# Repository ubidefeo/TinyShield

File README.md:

# TinyShield
A shield for programming ATTiny's from your Arduino

It's setup to just need 1 0805 Cap to put the Arduino into programming mode and a few headers to connect your Tiny's and to allow you to connect things easily to your tiny's once you've programmed them.

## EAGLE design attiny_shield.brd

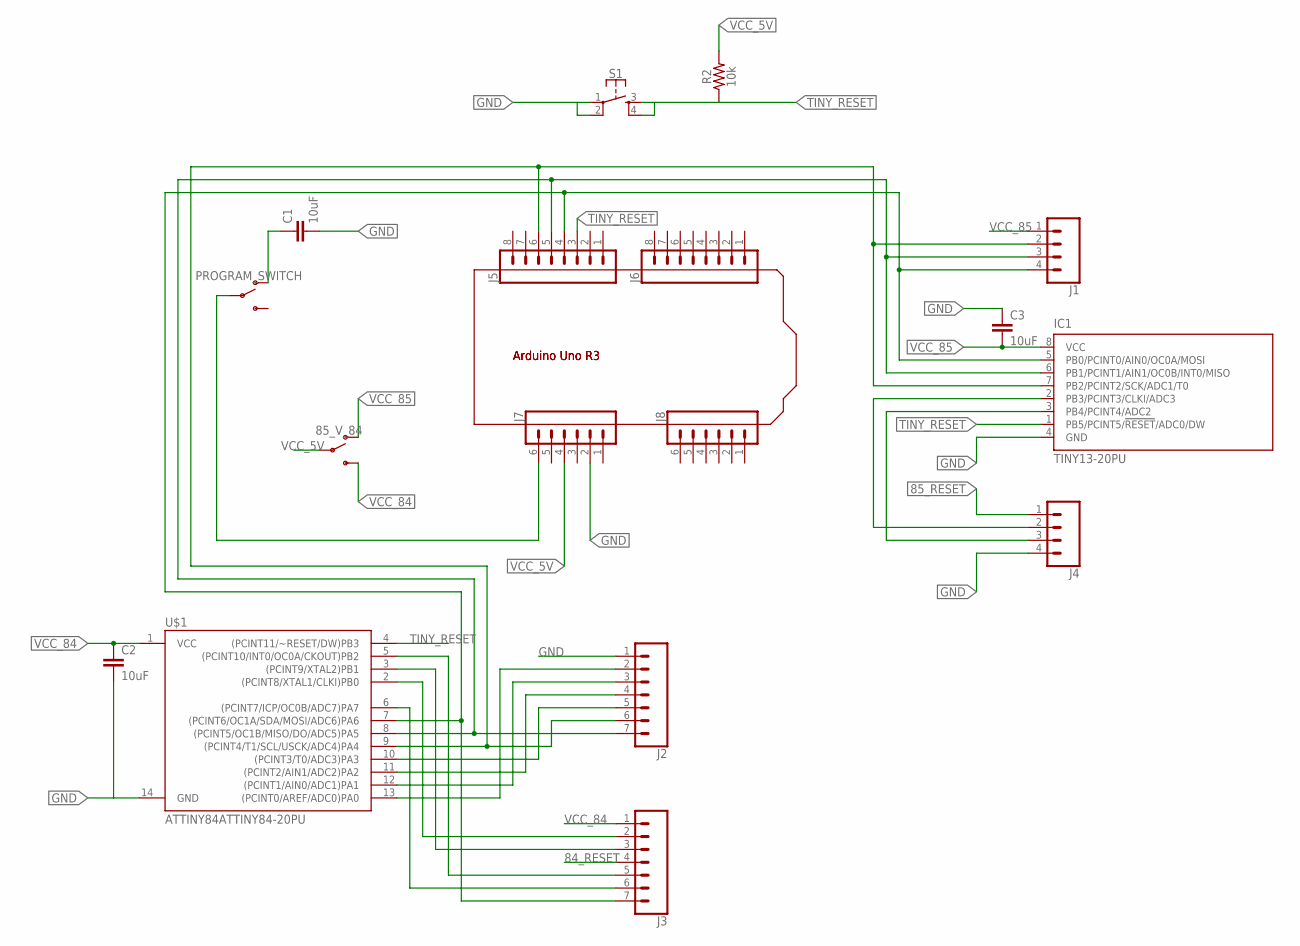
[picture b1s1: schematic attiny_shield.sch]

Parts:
85_V_84: SPARKFUN-SWITCHES_SWITCH-SPDT-SMD-AYZ0202; SPARKFUN-SWITCHES_SWITCH_DPDT_SMD_AYZ0202
C1, C2, C3: 10uF; 0805
IC1: TINY13-20PU; DIL08
J1, J4: CONN_04; 1X04
J2, J3: CONN_07; 1X07
J5, J6: CONN_08"; 1X08
J7, J8: CONN_06SILK_FEMALE_PTH; 1X06
PROGRAM_SWITCH: SWITCH-SPDT-SMD-AYZ0202; SWITCH_DPDT_SMD_AYZ0202
R2: 10k; SPARKFUN-RESISTORS_0603
S1: SPARKFUN-SWITCHES_MOMENTARY-SWITCH-SPST-2-SMD-5.2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; SPARKFUN-SWITCHES_TACTILE_SWITCH_SMD_5.2MM
U$1: ATTINY84ATTINY84-20PU; DIP14

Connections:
84_0: J2.2, U$1.13 ((PCINT0/AREF/ADC0)PA0)
84_1: J2.3, U$1.12 ((PCINT1/AIN0/ADC1)PA1)
84_RESET: J3.4
85_RESET: J4.1
GND: C1.2, C2.2, C3.1, IC1.4 (GND), J2.1, J4.4, J7.2, S1.1, S1.2, U$1.14 (GND)
MISO: IC1.6 (PB1/PCINT1/AIN1/OC0B/INT0/MISO), J1.3, J2.7, J5.5, U$1.8 ((PCINT5/OC1B/MISO/DO/ADC5)PA5)
MOSI: IC1.5 (PB0/PCINT0/AIN0/OC0A/MOSI), J1.4, J3.7, J5.4, U$1.7 ((PCINT6/OC1A/SDA/MOSI/ADC6)PA6)
unnamed: C1.1, PROGRAM_SWITCH.1 (O)
unnamed: IC1.2 (PB3/PCINT3/CLKI/ADC3), J4.2
unnamed: IC1.3 (PB4/PCINT4/ADC2), J4.3
unnamed: J7.6, PROGRAM_SWITCH.2
unnamed: J2.4, U$1.11 ((PCINT2/AIN1/ADC2)PA2)
unnamed: J2.5, U$1.10 ((PCINT3/T0/ADC3)PA3)
unnamed: J3.6, U$1.6 ((PCINT7/ICP/OC0B/ADC7)PA7)
unnamed: J3.2, U$1.2 ((PCINT8/XTAL1/CLKI)PB0)
unnamed: J3.3, U$1.3 ((PCINT9/XTAL2)PB1)
unnamed: J3.5, U$1.5 ((PCINT10/INT0/OC0A/CKOUT)PB2)
SCK: IC1.7 (PB2/PCINT2/SCK/ADC1/T0), J1.2, J2.6, J5.6, U$1.9 ((PCINT4/T1/SCL/USCK/ADC4)PA4)
TINY_RESET: IC1.1 (PB5/PCINT5/!RESET!/ADC0/DW), J5.3, R2.1, S1.3, S1.4, U$1.4 ((PCINT11/~RESET/DW)PB3)
VCC_5V: 85_V_84.2, J7.4, R2.2
VCC_84: 85_V_84.3 (S), C2.1, J3.1, U$1.1 (VCC)
VCC_85: 85_V_84.1 (O), C3.2, IC1.8 (VCC), J1.1

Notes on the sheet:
Arduino Uno R3

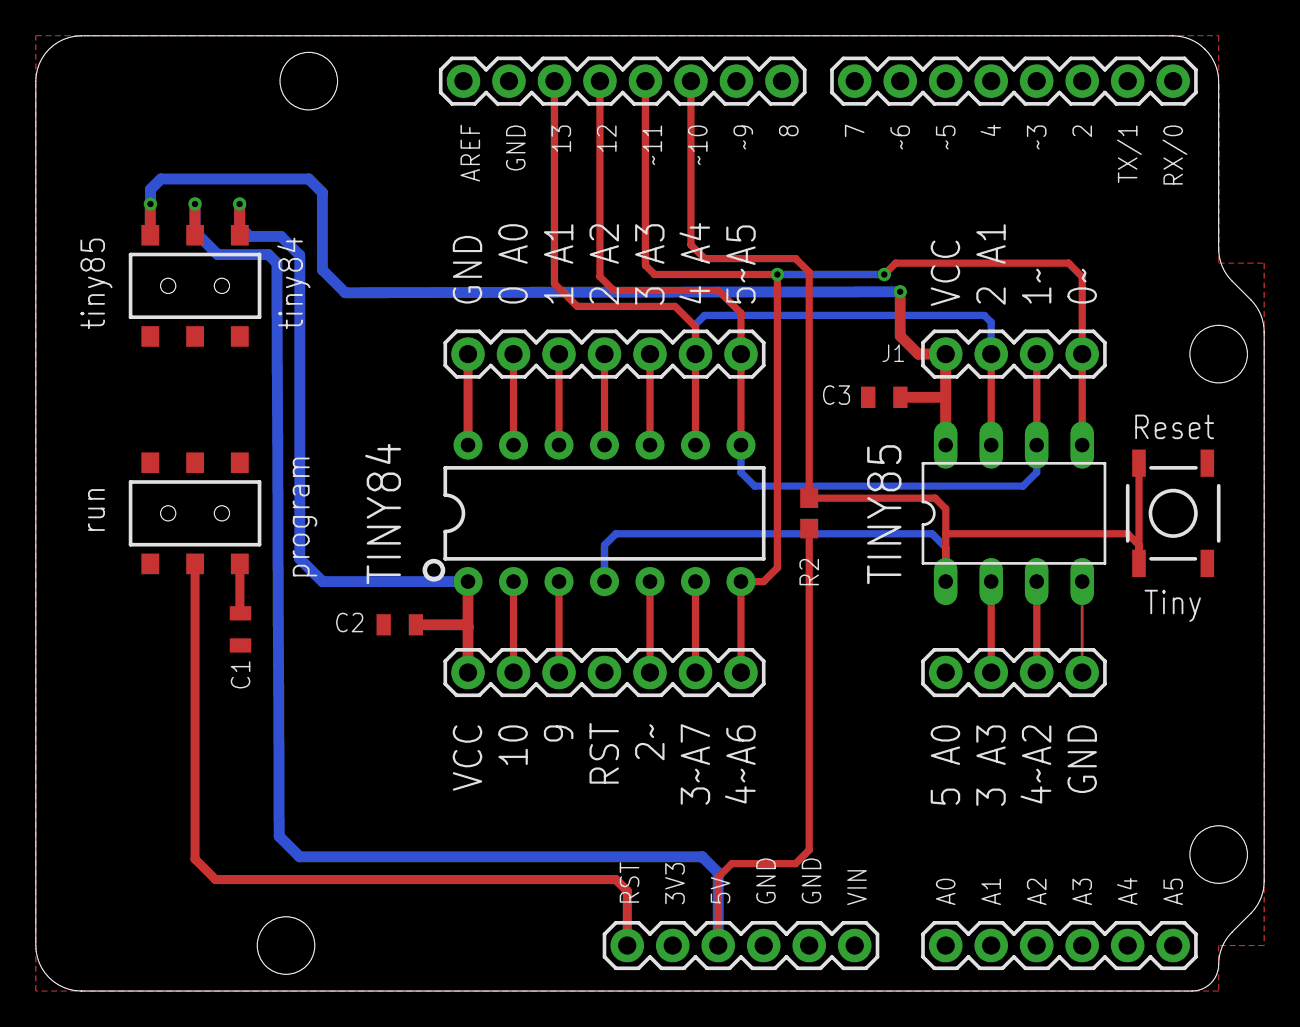
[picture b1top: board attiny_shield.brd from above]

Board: 2 copper layers, 68.6 x 53.3 mm, 17 parts (0 on the bottom side), 20 nets.

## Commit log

2018-02-09 initital commit
2018-02-09 gitignore update
2018-02-12 - first commit Ubi
2018-02-12 - clean-up
2018-02-12 added caps and pull-ups. added reset button.

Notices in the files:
parts and their libraries:
SparkFun-Switches: Licensing: Creative Commons ShareAlike 4.0 International - https://creativecommons.org/licenses/by-sa/4.0
